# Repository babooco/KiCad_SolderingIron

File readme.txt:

cewka 15 uh l2
cap 220uf rv3
1uf -> c10
c5 100 nf

proc
4.7 uf vcc

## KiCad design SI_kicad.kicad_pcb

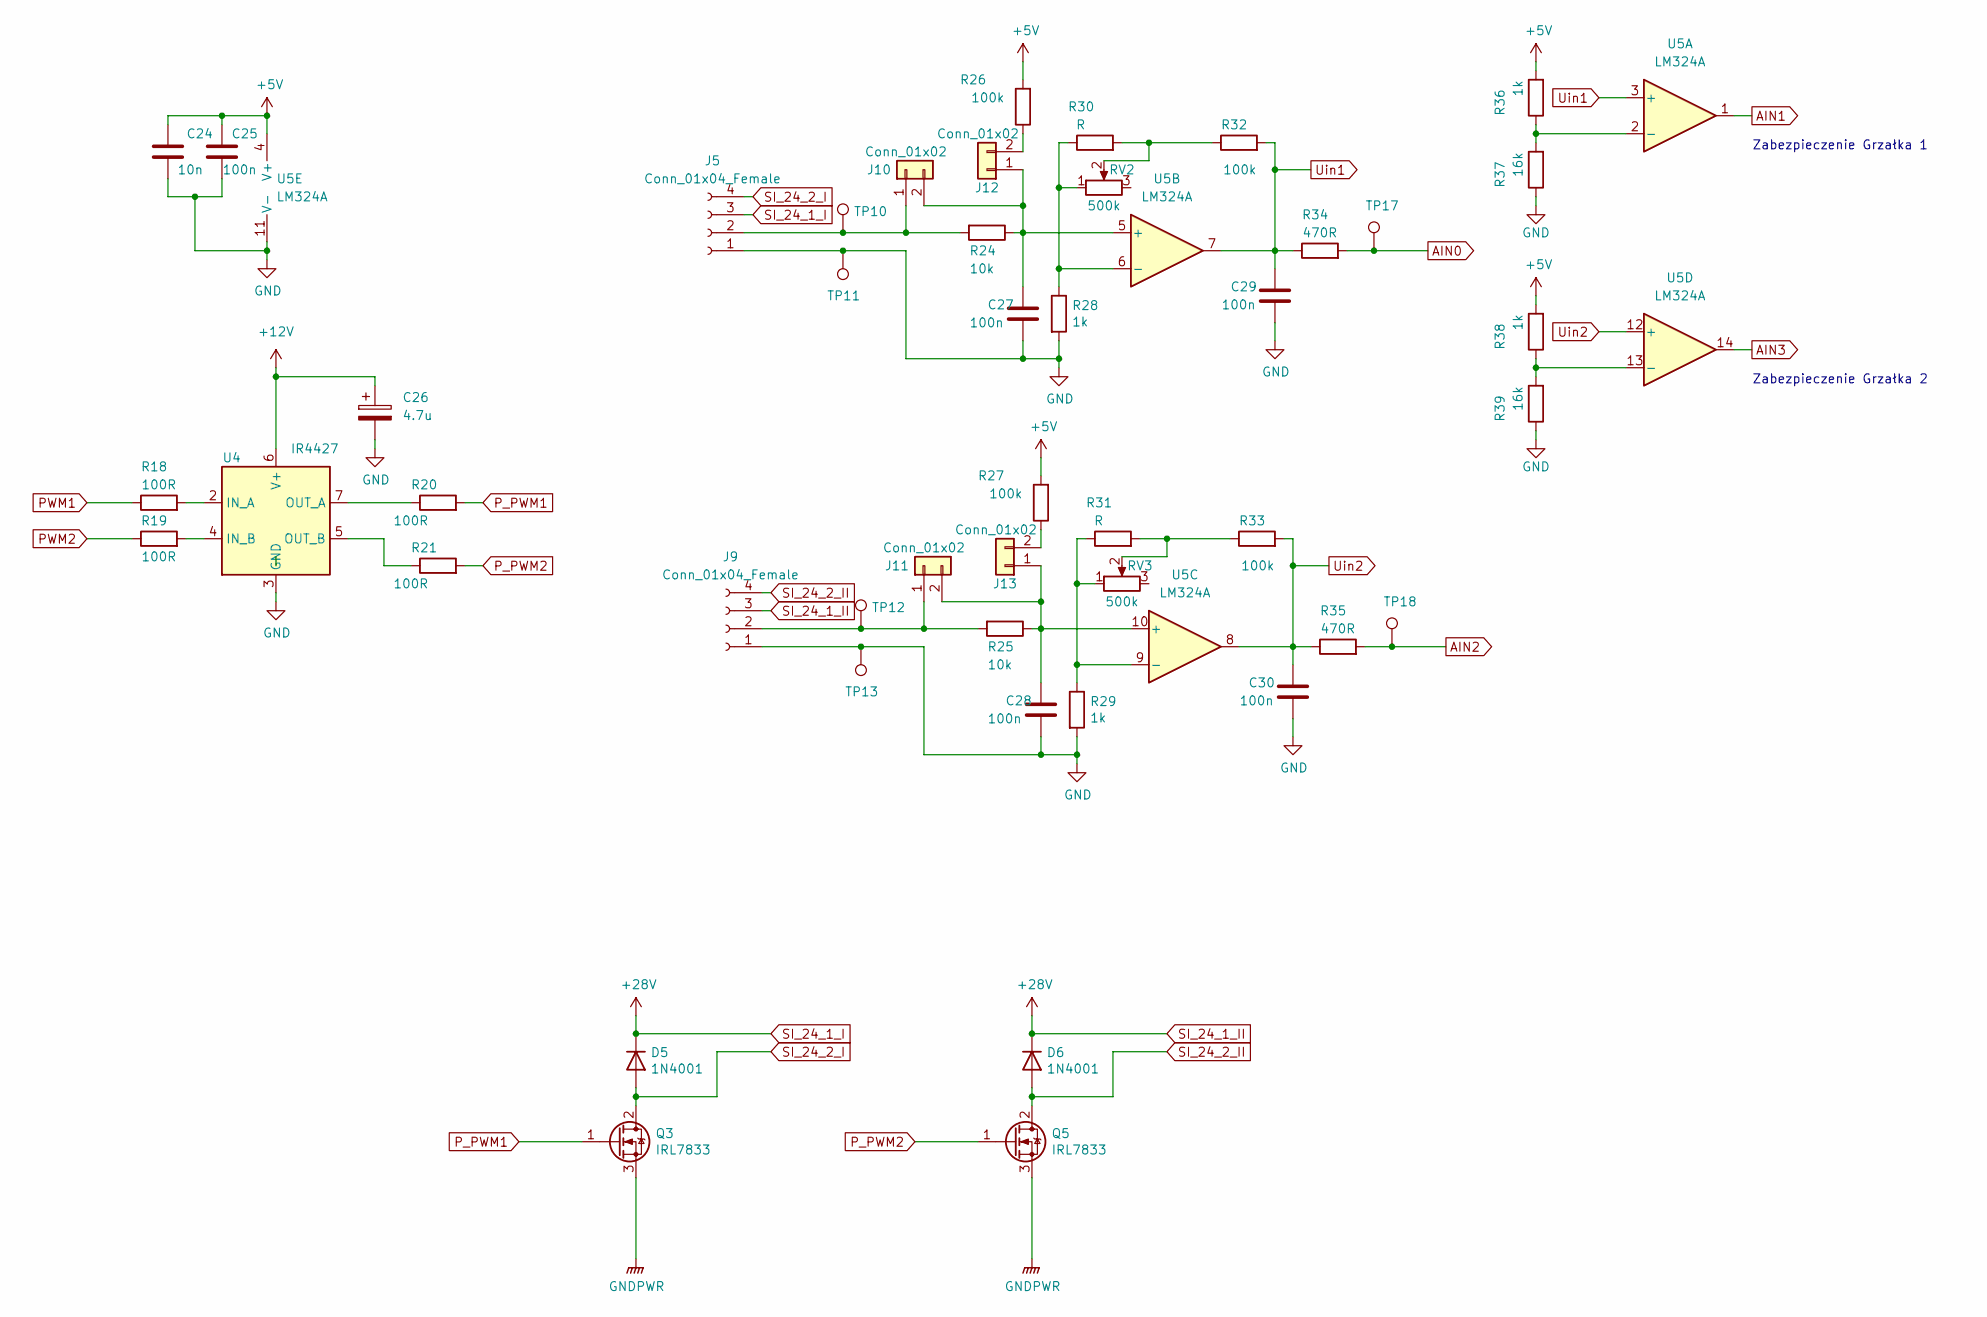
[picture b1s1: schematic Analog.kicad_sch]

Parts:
C24: 10n; C_0805_2012Metric_Pad1.18x1.45mm_HandSolder
C25, C27, C28, C29, C30: 100n; C_0805_2012Metric_Pad1.18x1.45mm_HandSolder
C26: 4.7u; CP_Elec_5x5.4
D5, D6: 1N4001; D_SMA
J5, J9: Conn_01x04_Female; JST_EH_B4B-EH-A_1x04_P2.50mm_Vertical
J10, J11, J12, J13: Conn_01x02; PinHeader_1x02_P2.54mm_Vertical
Q3, Q5: IRL7833; TO-220-3_Vertical
R18, R19, R20, R21: 100R; R_0805_2012Metric_Pad1.20x1.40mm_HandSolder
R24, R25: 10k; R_0805_2012Metric_Pad1.20x1.40mm_HandSolder
R26, R27, R32, R33: 100k; R_0805_2012Metric_Pad1.20x1.40mm_HandSolder
R28, R29, R36, R38: 1k; R_0805_2012Metric_Pad1.20x1.40mm_HandSolder
R30, R31: R; R_0805_2012Metric_Pad1.20x1.40mm_HandSolder
R34, R35: 470R; R_0805_2012Metric_Pad1.20x1.40mm_HandSolder
R37, R39: 16k; R_0805_2012Metric_Pad1.20x1.40mm_HandSolder
RV2, RV3: 500k; Potentiometer_Bourns_3296W_Vertical
TP10, TP11, TP12, TP13, TP17, TP18: TestPoint; TestPoint_Pad_D2.0mm
U4: IR4427; SOIC-8_3.9x4.9mm_P1.27mm
U5: LM324A; SO-14_3.9x8.65mm_P1.27mm

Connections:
+5V: C24.1, C25.1, R26.2, R27.2, R36.2, R38.2, U5.4 (V+); also elsewhere on the board
+12V: C26.1, U4.6 (V+); also elsewhere on the board
AIN0: R34.2, TP17.1; also elsewhere on the board
AIN1: U5.1; also elsewhere on the board
AIN2: R35.2, TP18.1; also elsewhere on the board
AIN3: U5.14; also elsewhere on the board
GND: C24.2, C25.2, C26.2, C27.2, C28.2, C29.2, C30.2, J5.1, J9.1, R28.2, R29.2, R37.1, R39.1, TP11.1, TP13.1, U4.3 (GND), U5.11 (V-); also elsewhere on the board
GNDPWR: Q3.3 (S), Q5.3 (S); also elsewhere on the board
unnamed: J5.2, J10.1, R24.2, TP10.1
unnamed: C27.1, J10.2, J12.1, R24.1, U5.5 (+)
unnamed: J9.2, J11.1, R25.2, TP12.1
unnamed: C28.1, J11.2, J13.1, R25.1, U5.10 (+)
unnamed: J12.2, R26.1
unnamed: J13.2, R27.1
unnamed: R30.2, R32.1, RV2.2
unnamed: R31.2, R33.1, RV3.2
unnamed: R18.2, U4.2 (IN_A)
unnamed: R19.2, U4.4 (IN_B)
unnamed: R20.1, U4.7 (OUT_A)
unnamed: R21.1, U4.5 (OUT_B)
unnamed: R36.1, R37.2, U5.2 (-)
unnamed: R28.1, R30.1, RV2.1, U5.6 (-)
unnamed: R29.1, R31.1, RV3.1, U5.9 (-)
unnamed: R38.1, R39.2, U5.13 (-)
PWM1: R18.1; also elsewhere on the board
PWM2: R19.1; also elsewhere on the board
P_PWM1: Q3.1 (G), R20.2
P_PWM2: Q5.1 (G), R21.2
SI_24_1_I: D5.1 (K), D6.1 (K), J5.3, J9.3; also elsewhere on the board
SI_24_2_I: D5.2 (A), J5.4, Q3.2 (D)
SI_24_2_II: D6.2 (A), J9.4, Q5.2 (D)
Uin1: C29.1, R32.2, R34.1, U5.3 (+), U5.7
Uin2: C30.1, R33.2, R35.1, U5.8, U5.12 (+)

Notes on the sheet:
Zabezpieczenie Grzałka 1
Zabezpieczenie Grzałka 2

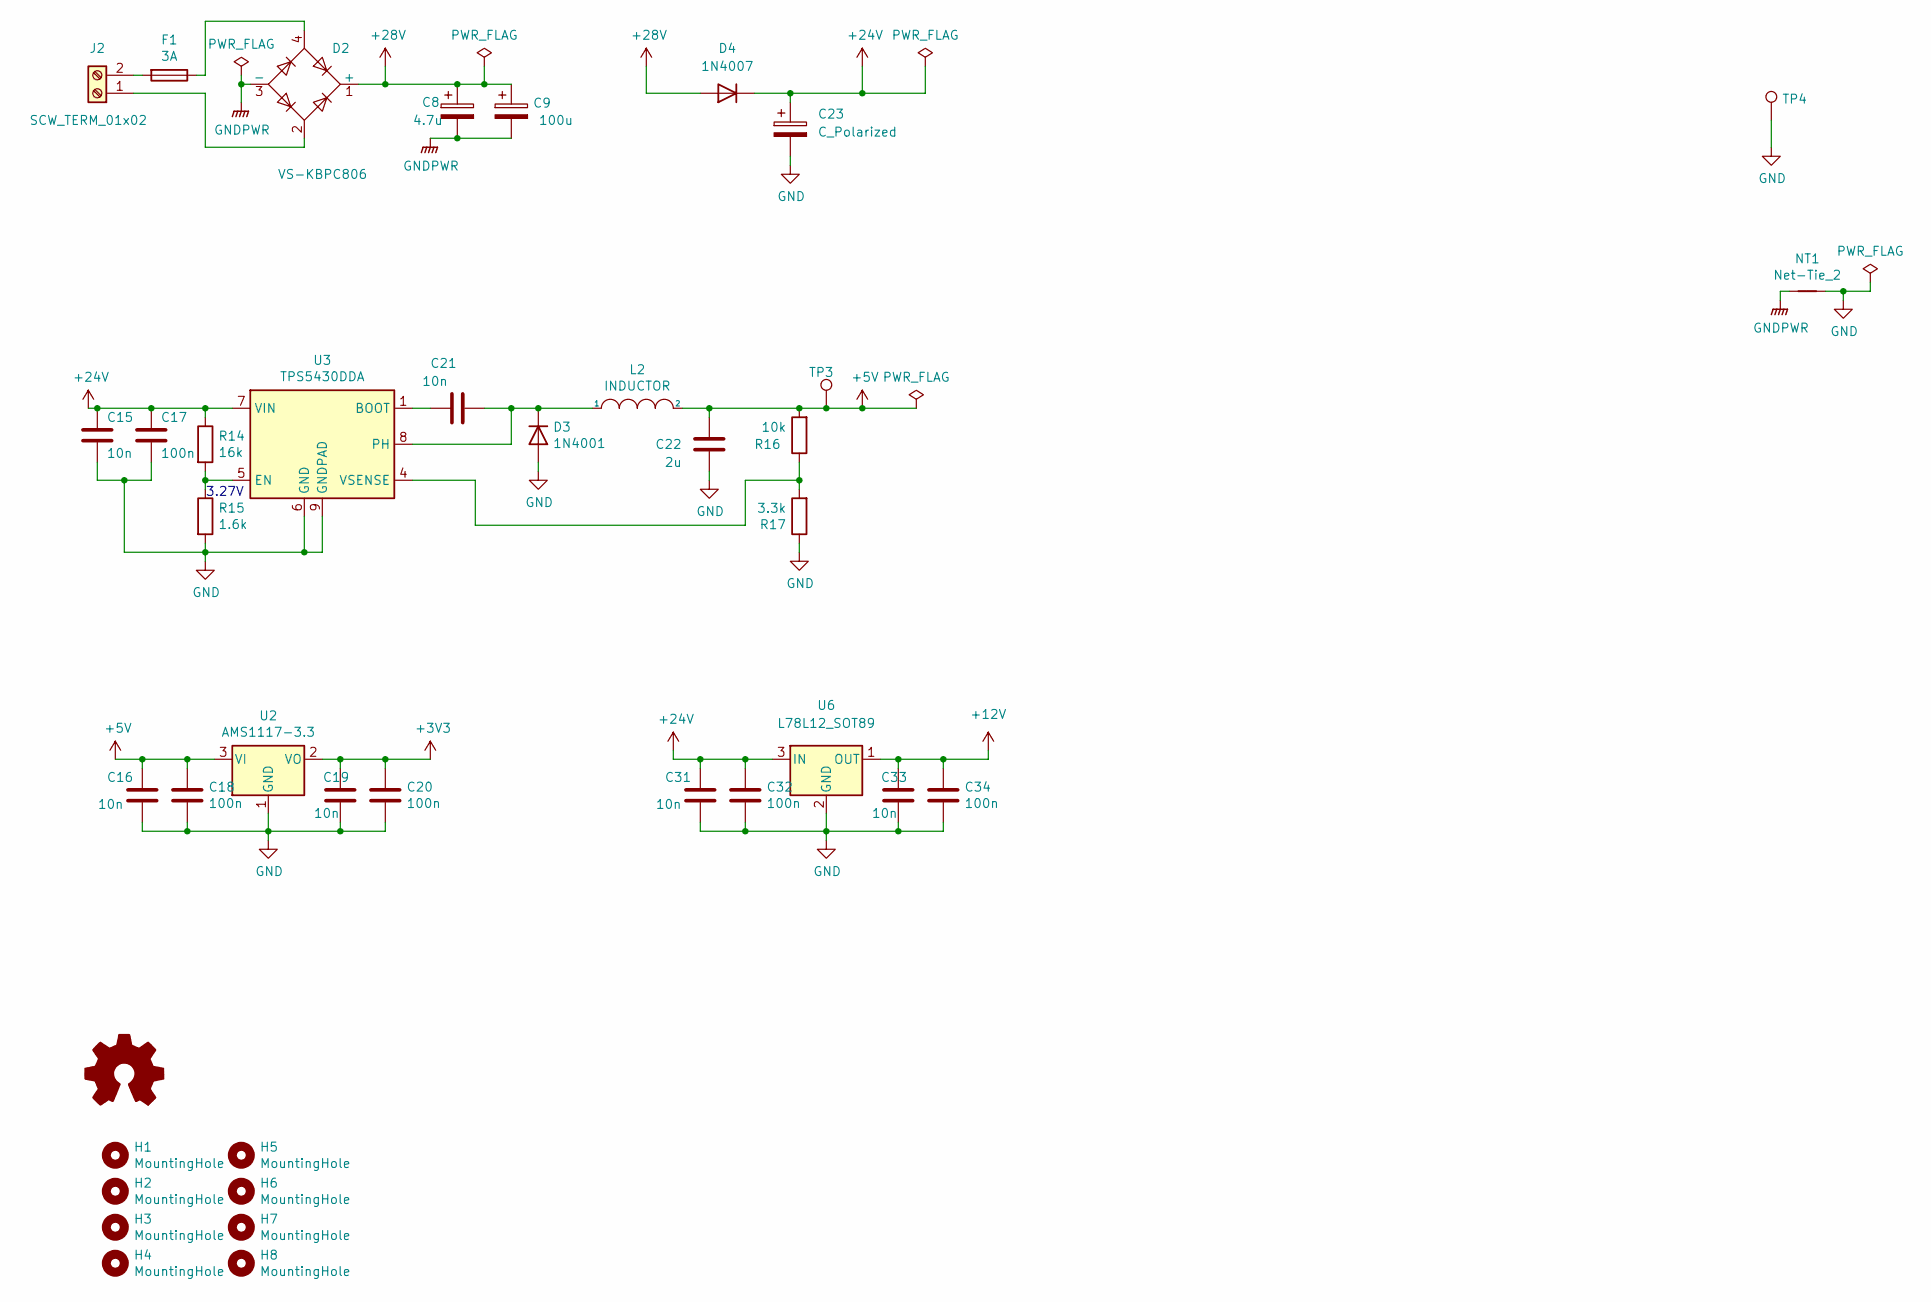
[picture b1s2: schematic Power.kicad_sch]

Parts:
C8: 4.7u; CP_Radial_D5.0mm_P2.50mm
C9: 100u; CP_Radial_D6.3mm_P2.50mm
C15, C16, C19, C21, C31, C33: 10n; C_0805_2012Metric_Pad1.18x1.45mm_HandSolder
C17, C18, C20, C32, C34: 100n; C_0805_2012Metric_Pad1.18x1.45mm_HandSolder
C22: 2u; C_0805_2012Metric_Pad1.18x1.45mm_HandSolder
C23: C_Polarized; CP_Radial_D6.3mm_P2.50mm
D2: VS-KBPC806; Diode_Bridge_Vishay_KBPC6
D3: 1N4001; D_SMA
D4: 1N4007; D_SMA
F1: 3A; Fuseholder_Cylinder-5x20mm_Schurter_0031_8201_Horizontal_Op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
H1, H2, H3, H4, H5, H6, H7, H8: MountingHole; MountingHole_2.7mm_M2.5_DIN965_Pad
H9: Logo_Open_Hardware_Small; OSHW-Logo_5.7x6mm_Copper
J2: SCW_TERM_01x02; TerminalBlock_Phoenix_MKDS-1,5-2-5.08_1x02_P5.08mm_Horizont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
L2: INDUCTOR; L_Coilcraft_LPS4018
NT1: Net-Tie_2; NetTie-2_SMD_Pad0.5mm
R14: 16k; R_0805_2012Metric_Pad1.20x1.40mm_HandSolder
R15: 1.6k; R_0805_2012Metric_Pad1.20x1.40mm_HandSolder
R16: 10k; R_0805_2012Metric_Pad1.20x1.40mm_HandSolder
R17: 3.3k; R_0805_2012Metric_Pad1.20x1.40mm_HandSolder
TP3, TP4: TestPoint; TestPoint_Pad_D2.0mm
U2: AMS1117-3.3; SOT-223
U3: TPS5430DDA; TI_SO-PowerPAD-8_ThermalVias
U6: L78L12_SOT89; SOT-89-3

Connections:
+3V3: C19.1, C20.1, U2.2 (VO); also elsewhere on the board
+5V: C16.1, C18.1, C22.2, L2.2, R16.2, TP3.1, U2.3 (VI); also elsewhere on the board
+12V: C33.1, C34.1, U6.1 (OUT); also elsewhere on the board
+24V: C15.1, C17.1, C23.1, C31.1, C32.1, D4.1 (K), R14.1, U3.7 (VIN), U6.3 (IN)
GND: C15.2, C16.2, C17.2, C18.2, C19.2, C20.2, C22.1, C23.2, C31.2, C32.2, C33.2, C34.2, D3.2 (A), NT1.2, R15.2, R17.1, TP4.1, U2.1 (GND), U3.6 (GND), U3.9 (GNDPAD), U6.2 (GND); also elsewhere on the board
GNDPWR: C8.2, C9.2, D2.3 (-), NT1.1; also elsewhere on the board
unnamed: D2.4, F1.1
unnamed: C21.2, D3.1 (K), L2.1, U3.8 (PH)
unnamed: D2.2, J2.1
unnamed: F1.2, J2.2
unnamed: C21.1, U3.1 (BOOT)
unnamed: R14.2, R15.1, U3.5 (EN)
unnamed: R16.1, R17.2, U3.4 (VSENSE)
SI_24_1_I: C8.1, C9.1, D2.1 (+), D4.2 (A); also elsewhere on the board

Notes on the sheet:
3.27V

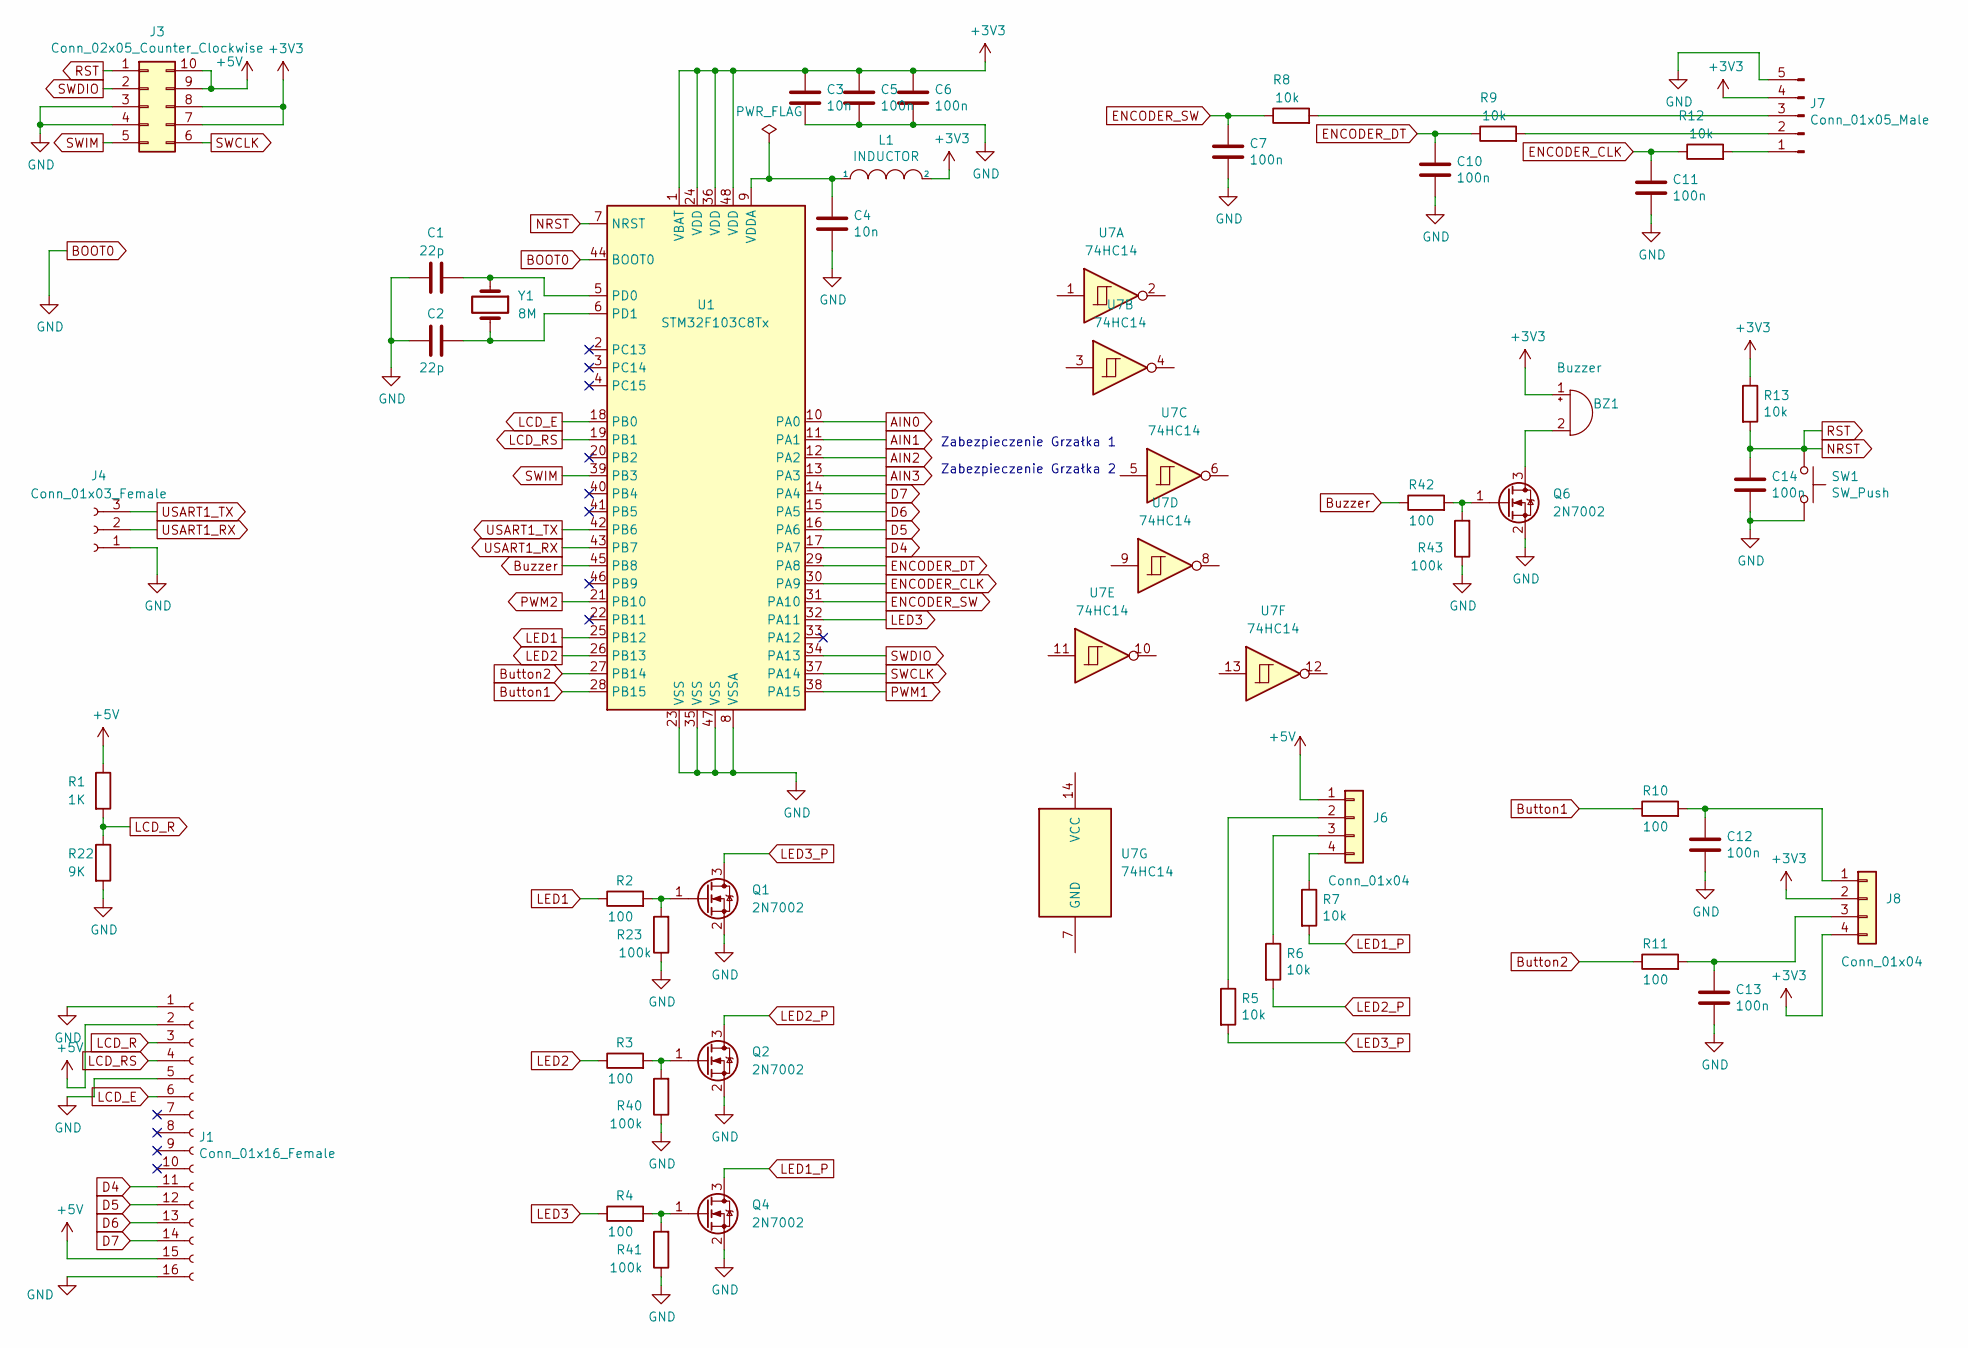
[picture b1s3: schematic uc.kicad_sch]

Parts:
BZ1: Buzzer; Buzzer_12x9.5RM7.6
C1, C2: 22p; C_0805_2012Metric_Pad1.18x1.45mm_HandSolder
C3, C4: 10n; C_0805_2012Metric_Pad1.18x1.45mm_HandSolder
C5, C6, C7, C10, C11, C12, C13, C14: 100n; C_0805_2012Metric_Pad1.18x1.45mm_HandSolder
J1: Conn_01x16_Female; PinSocket_1x16_P2.54mm_Vertical
J3: Conn_02x05_Counter_Clockwise; PinHeader_2x05_P2.54mm_Vertical
J4: Conn_01x03_Female; JST_EH_B3B-EH-A_1x03_P2.50mm_Vertical
J6, J8: Conn_01x04; JST_EH_B4B-EH-A_1x04_P2.50mm_Vertical
J7: Conn_01x05_Male; JST_EH_B5B-EH-A_1x05_P2.50mm_Vertical
L1: INDUCTOR; L_0805_2012Metric
Q1, Q2, Q4, Q6: 2N7002; SOT-23
R1: 1K; R_0805_2012Metric_Pad1.20x1.40mm_HandSolder
R2, R3, R4, R10, R11, R42: 100; R_0805_2012Metric_Pad1.20x1.40mm_HandSolder
R5, R6, R7, R8, R9, R12, R13: 10k; R_0805_2012Metric_Pad1.20x1.40mm_HandSolder
R22: 9K; R_0805_2012Metric_Pad1.20x1.40mm_HandSolder
R23, R40, R41, R43: 100k; R_0805_2012Metric_Pad1.20x1.40mm_HandSolder
SW1: SW_Push; SW_SPST_EVQPE1
U1: STM32F103C8Tx; LQFP-48_7x7mm_P0.5mm
U7: 74HC14
Y1: 8M; Resonator-2Pin_W10.0mm_H5.0mm

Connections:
+3V3: BZ1.1 (-), C3.1, C5.1, C6.1, J3.7, J3.8, J7.4, J8.2, J8.4, L1.2, R13.1, U1.1 (VBAT), U1.24 (VDD), U1.36 (VDD), U1.48 (VDD); also elsewhere on the board
+5V: J1.2, J1.15, J3.9, J3.10, J6.1, R1.1; also elsewhere on the board
AIN0: U1.10 (PA0); also elsewhere on the board
AIN1: U1.11 (PA1); also elsewhere on the board
AIN2: U1.12 (PA2); also elsewhere on the board
AIN3: U1.13 (PA3); also elsewhere on the board
Button1: R10.1, U1.28 (PB15)
Button2: R11.1, U1.27 (PB14)
Buzzer: R42.1, U1.45 (PB8)
D4: J1.11, U1.17 (PA7)
D5: J1.12, U1.16 (PA6)
D6: J1.13, U1.15 (PA5)
D7: J1.14, U1.14 (PA4)
ENCODER_CLK: C11.1, R12.1, U1.30 (PA9)
ENCODER_DT: C10.1, R9.1, U1.29 (PA8)
ENCODER_SW: C7.1, R8.1, U1.31 (PA10)
GND: C1.1, C2.1, C3.2, C4.2, C5.2, C6.2, C7.2, C10.2, C11.2, C12.2, C13.2, C14.2, J1.1, J1.5, J1.16, J3.3, J3.4, J4.1, J7.5, Q1.2 (S), Q2.2 (S), Q4.2 (S), Q6.2 (S), R22.2, R23.1, R40.1, R41.1, R43.1, SW1.2, U1.8 (VSSA), U1.23 (VSS), U1.35 (VSS), U1.44 (BOOT0), U1.47 (VSS); also elsewhere on the board
LCD_E: J1.6, U1.18 (PB0)
LCD_R: J1.3, R1.2, R22.1
LCD_RS: J1.4, U1.19 (PB1)
LED1: R2.1, U1.25 (PB12)
LED1_P: Q4.3 (D), R7.2
LED2: R3.1, U1.26 (PB13)
LED2_P: Q2.3 (D), R6.2
LED3: R4.1, U1.32 (PA11)
LED3_P: Q1.3 (D), R5.2
NRST: C14.1, J3.1, R13.2, SW1.1, U1.7 (NRST)
unnamed: BZ1.2 (+), Q6.3 (D)
unnamed: J6.2, R5.1
unnamed: J6.3, R6.1
unnamed: J6.4, R7.1
unnamed: J7.1, R12.2
unnamed: J7.2, R9.2
unnamed: J7.3, R8.2
unnamed: C12.1, J8.1, R10.2
unnamed: C13.1, J8.3, R11.2
unnamed: Q1.1 (G), R2.2, R23.2
unnamed: Q2.1 (G), R3.2, R40.2
unnamed: Q4.1 (G), R4.2, R41.2
unnamed: Q6.1 (G), R42.2, R43.2
unnamed: C1.2, U1.5 (PD0), Y1.1
unnamed: C2.2, U1.6 (PD1), Y1.2
unnamed: C4.1, L1.1, U1.9 (VDDA)
PWM1: U1.38 (PA15); also elsewhere on the board
PWM2: U1.21 (PB10); also elsewhere on the board
SWCLK: J3.6, U1.37 (PA14)
SWDIO: J3.2, U1.34 (PA13)
SWIM: J3.5, U1.39 (PB3)
USART1_RX: J4.2, U1.43 (PB7)
USART1_TX: J4.3, U1.42 (PB6)

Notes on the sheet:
Zabezpieczenie Grzałka 2
Zabezpieczenie Grzałka 1

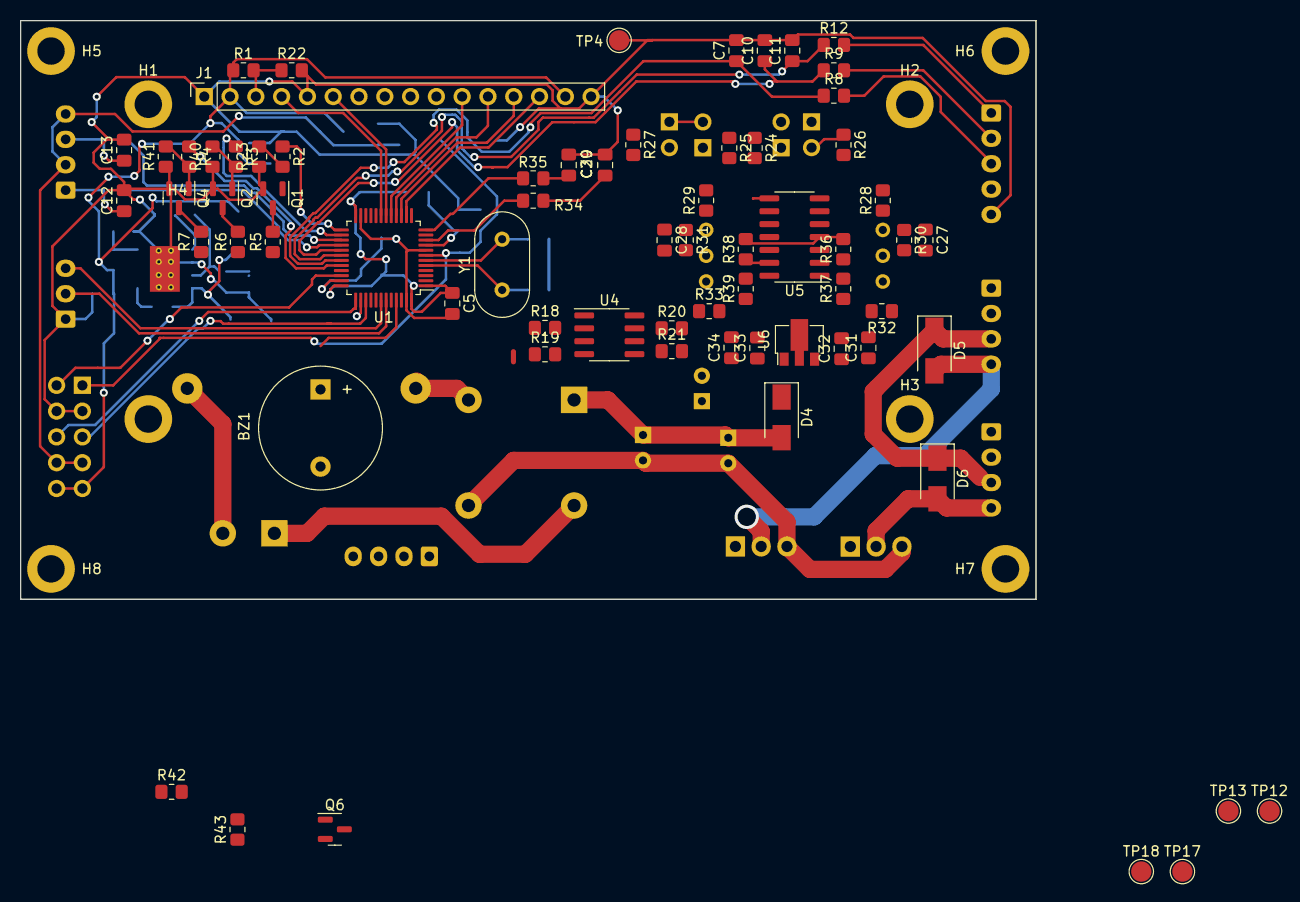
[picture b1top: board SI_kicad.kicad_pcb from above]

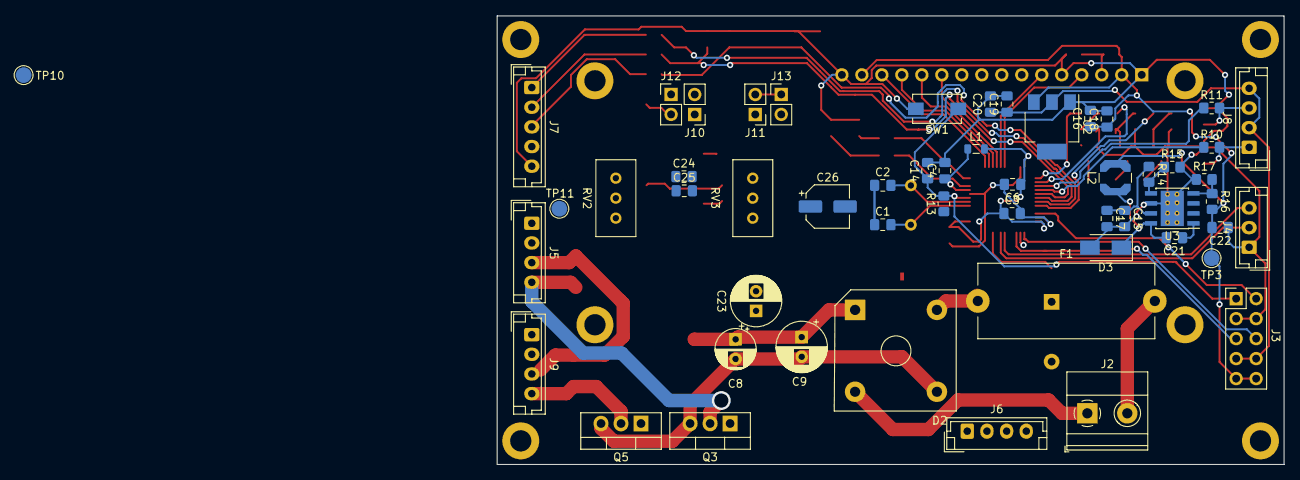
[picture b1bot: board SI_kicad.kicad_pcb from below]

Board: 2 copper layers, 100.0 x 57.0 mm, 133 parts (54 on the bottom side), 83 nets.

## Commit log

2023-02-20 1.2 Update schematic to kicad 6
